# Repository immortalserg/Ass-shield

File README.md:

# Ass-shield
## Плата расширения для OrangePi Zero, OrangePi Zero plus, OrangePi Zero plus2, NanoPi Neo, NanoPi Neo Air, NanoPi Neo 2, NanoPi Neo Core, NanoPi Neo Core2, RaspberryPi Zero, BananaPi zero
### Функции
- Массив из 4-х микрофонов через процессор ADAU1772
- RF315/433 МГц приемник/передатчик (м.cx. SYN480R и SYN115)
- NRF24L01+
- zigbee cc2530 + cc2591
- 12 светодиодов WS2812B
- звук i2s ES9023 (только NanoPi) c усилителем 2х3Вт PAM8403 (PAM8404)
- часы реального времени DS3231
- 4 ИК светодиода для управления техникой
- диаметр 80 мм
- поддержска протокола Z-wave (USB stick или UART)
## Описание
- ИК передатчики (4 ИК диода через транзистор) подключены к GPIO26 (PA10) /NanoPi - PA0/
- 433 МГц приемник - GPIO15 (PA03) 
- 433 МГц передатчик - GPIO18 (PA18) /NanoPi PG8/
- 315 МГц приемник - GPIO12 (PA07) /NanoPi PG11/
- 315 МГц передатчик - GPIO16 (PA19) /NanoPi PG9/
- SI4432 - SPI1 (MOSI-GPIO19, MISO-GPIO21, CLK-GPIO23, NIRQ-GPIO13, NSEL-GPIO11)
- nrf24l01+ - SPI1 (MOSI-GPIO19, MISO-GPIO21, CLK-GPIO23, CS-GPIO24) /NanoPi SPI0 (MOSI-PC0, MISO-PC1, CLK-PC2, CS-PC3)/
- zigbee (cc2530) с усилителем cc2591 - UART1
- WS2812 LED - GPIO7 (PA06) 
- Часы реального времени DS3231 - i2c0
- i2c PCF8574 (P0- управление режимом записи 24LC256, P1-P4 - входы ADAU1772, P5 - MUTE  P6&P7 - Gain Select) 

Программирование ADAU1772 через i2c запись на микросхему памяти 24LC256, программирование: цифровые входы микрофонов, выходы аналоговые для OrangePi Zero, для остальных выход i2s в режиме ведомого.

J1 - питание 6-40V (1-VCC, 2-GND) на DC-DC преобразователь

J2 - DEBUG разъем для программирования cc2530 через (1-DC,2-DD,3-Reset,4-3.3V,5-GND)

J3 - питание 5В с DC-DC преобразователя (установить перемычку для питания через DC-DC преобразователь)

J4 - UART2 (1-3.3V, 2-RX, 3-TX, 4-GND) /нет для RaspberryPi Zero/

J5 - антенна NRF24L01+

J6 - i2s (1-WS, 2-CLK, 3-DIN) ADAU1772

J7 - выход на динамики (1-L+, 2-L-, 3-R+, 4-R-)

J8 - антенна zigbee (cc2530+cc2591)

### Переходная плата NanoPi Neo

J1 - переключение выхода звука 1,2-ON;3,4-OFF -- LINE / 1,2-OFF;3,4-ON -- i2s ES9023

### Переходная плата BananaPi zero, RaspberryPi Zero

J3 - переключатель i2s BananaPi Zero / RaspberryPi Zero

Для RaspberryPi Zero не используется LAN и UART2

## Изображения

## Переходная плата для NanoPi Neo

### Переходная плата BananaPi zero, RaspberryPi Zero

## Корпус

,

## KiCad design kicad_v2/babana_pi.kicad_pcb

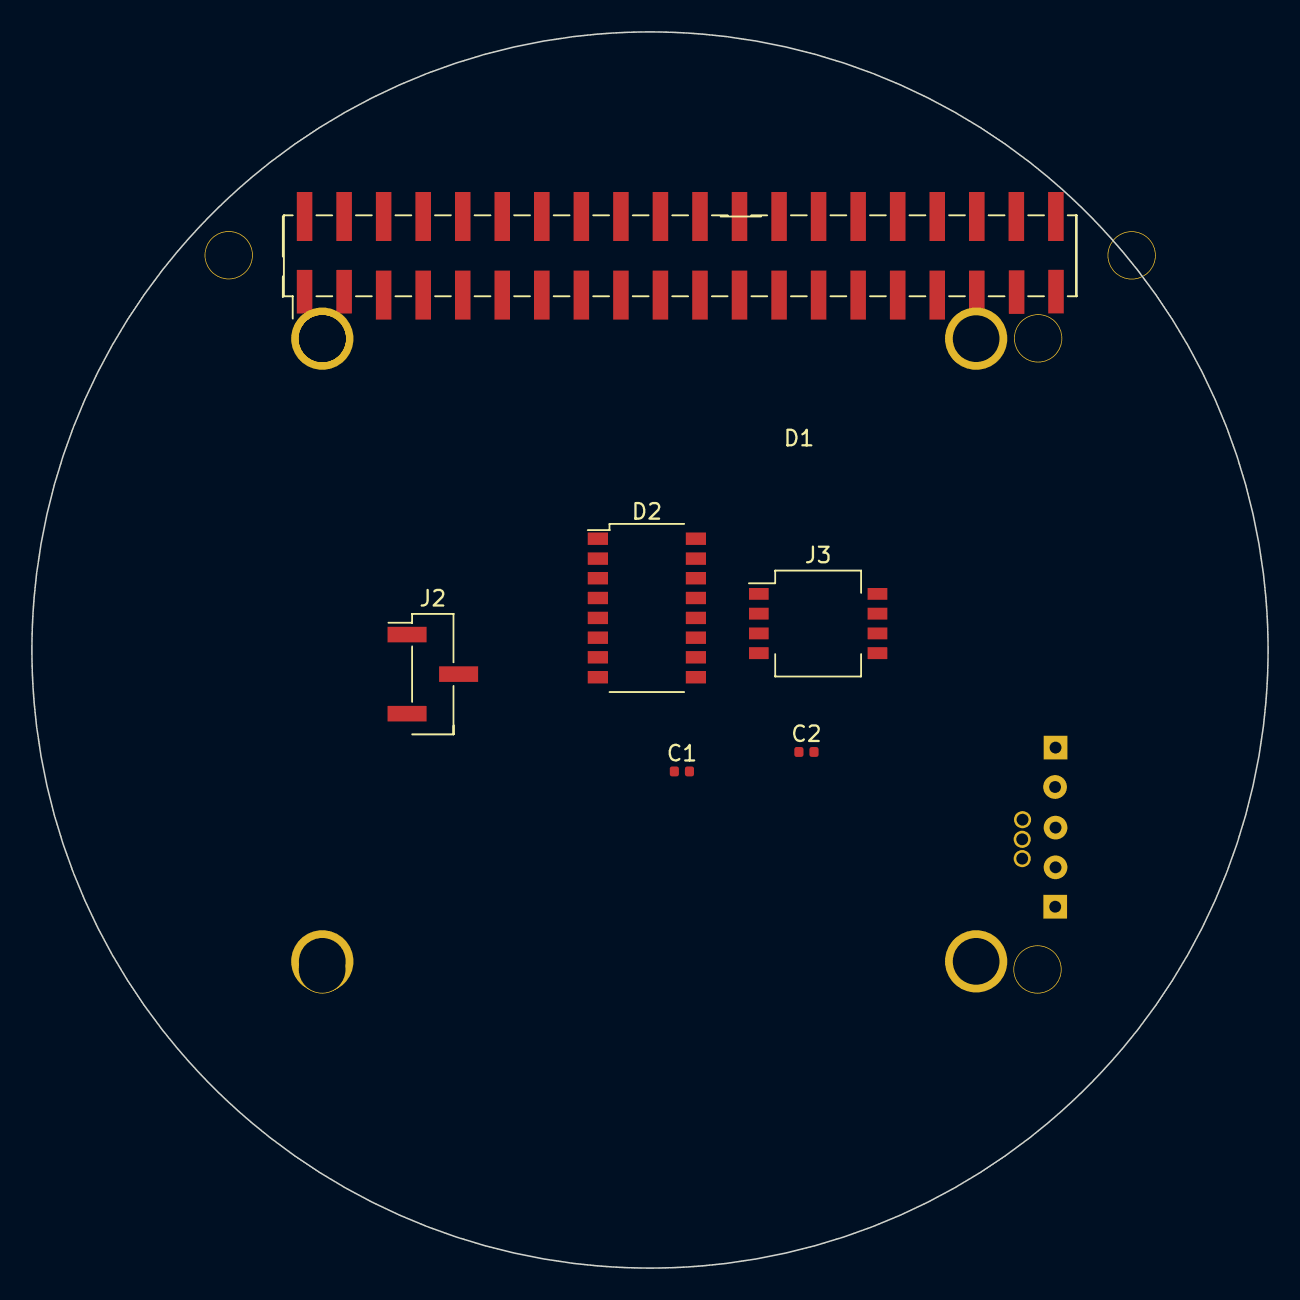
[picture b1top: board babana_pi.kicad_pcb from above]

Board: 2 copper layers, 79.4 x 79.4 mm, 7 parts (1 on the bottom side), 34 nets, no tracks yet.

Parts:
C1, C2: 1 µF; C_0402_1005Metric
D1: BananaPi
D2: ES9023; SOP-16_4.4x10.4mm_P1.27mm
J2: i2s; PinHeader_1x03_P2.54mm_Vertical_SMD_Pin1Left
J3: BananaPi/RaspberryPi; SW_DIP_SPSTx04_Slide_KingTek_DSHP04TS_W7.62mm_P1.27mm
U1: OPiZero-imm_lib; OPiZeroSMD

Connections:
3,3V: D1.17, D2.5, D2.6, U1.101
5V: D1.4, U1.102, U1.104
GND: C2.2, D2.12, D2.14, U1.2, U1.106, U1.109, U1.114, U1.120, U1.125, U1.201
IR: D1.18, U1.13
LL: D2.7, U1.8
LR: D2.8, U1.7
unnamed: C1.1, D2.10
unnamed: C1.2, D2.9
unnamed: C2.1, D2.11
unnamed: D1.12, J3.8
unnamed: D1.27, J3.5
unnamed: D1.28, J3.6
unnamed: D1.35, J3.7
PA02: D1.22, U1.122
PA03: D1.15, U1.115
PA07: D1.29, U1.112
PA10: D1.26, U1.126
PA18: D1.31, U1.118
PA19: D1.33, U1.116
PWM1: D1.7, U1.107
SCK: D1.5, U1.105
SDA: D1.3, U1.103
SPI1_CLK: D1.23, U1.123
SPI1_CS: D1.24, U1.124
SPI1_MISO: D1.21, U1.121
SPI1_MOSI: D1.19, U1.119
UART1_RX: D1.10, U1.110
UART1_TX: D1.8, U1.108
UART2_RX: D1.11, U1.111
UART2_TX: D1.13, U1.113
i2s-DIN: D1.38, J2.3
i2s_CLK: D2.1, J2.2, J3.2, J3.4
i2s_SDI: D1.40, D2.3
i2s_WS: D2.2, J2.1, J3.1, J3.3

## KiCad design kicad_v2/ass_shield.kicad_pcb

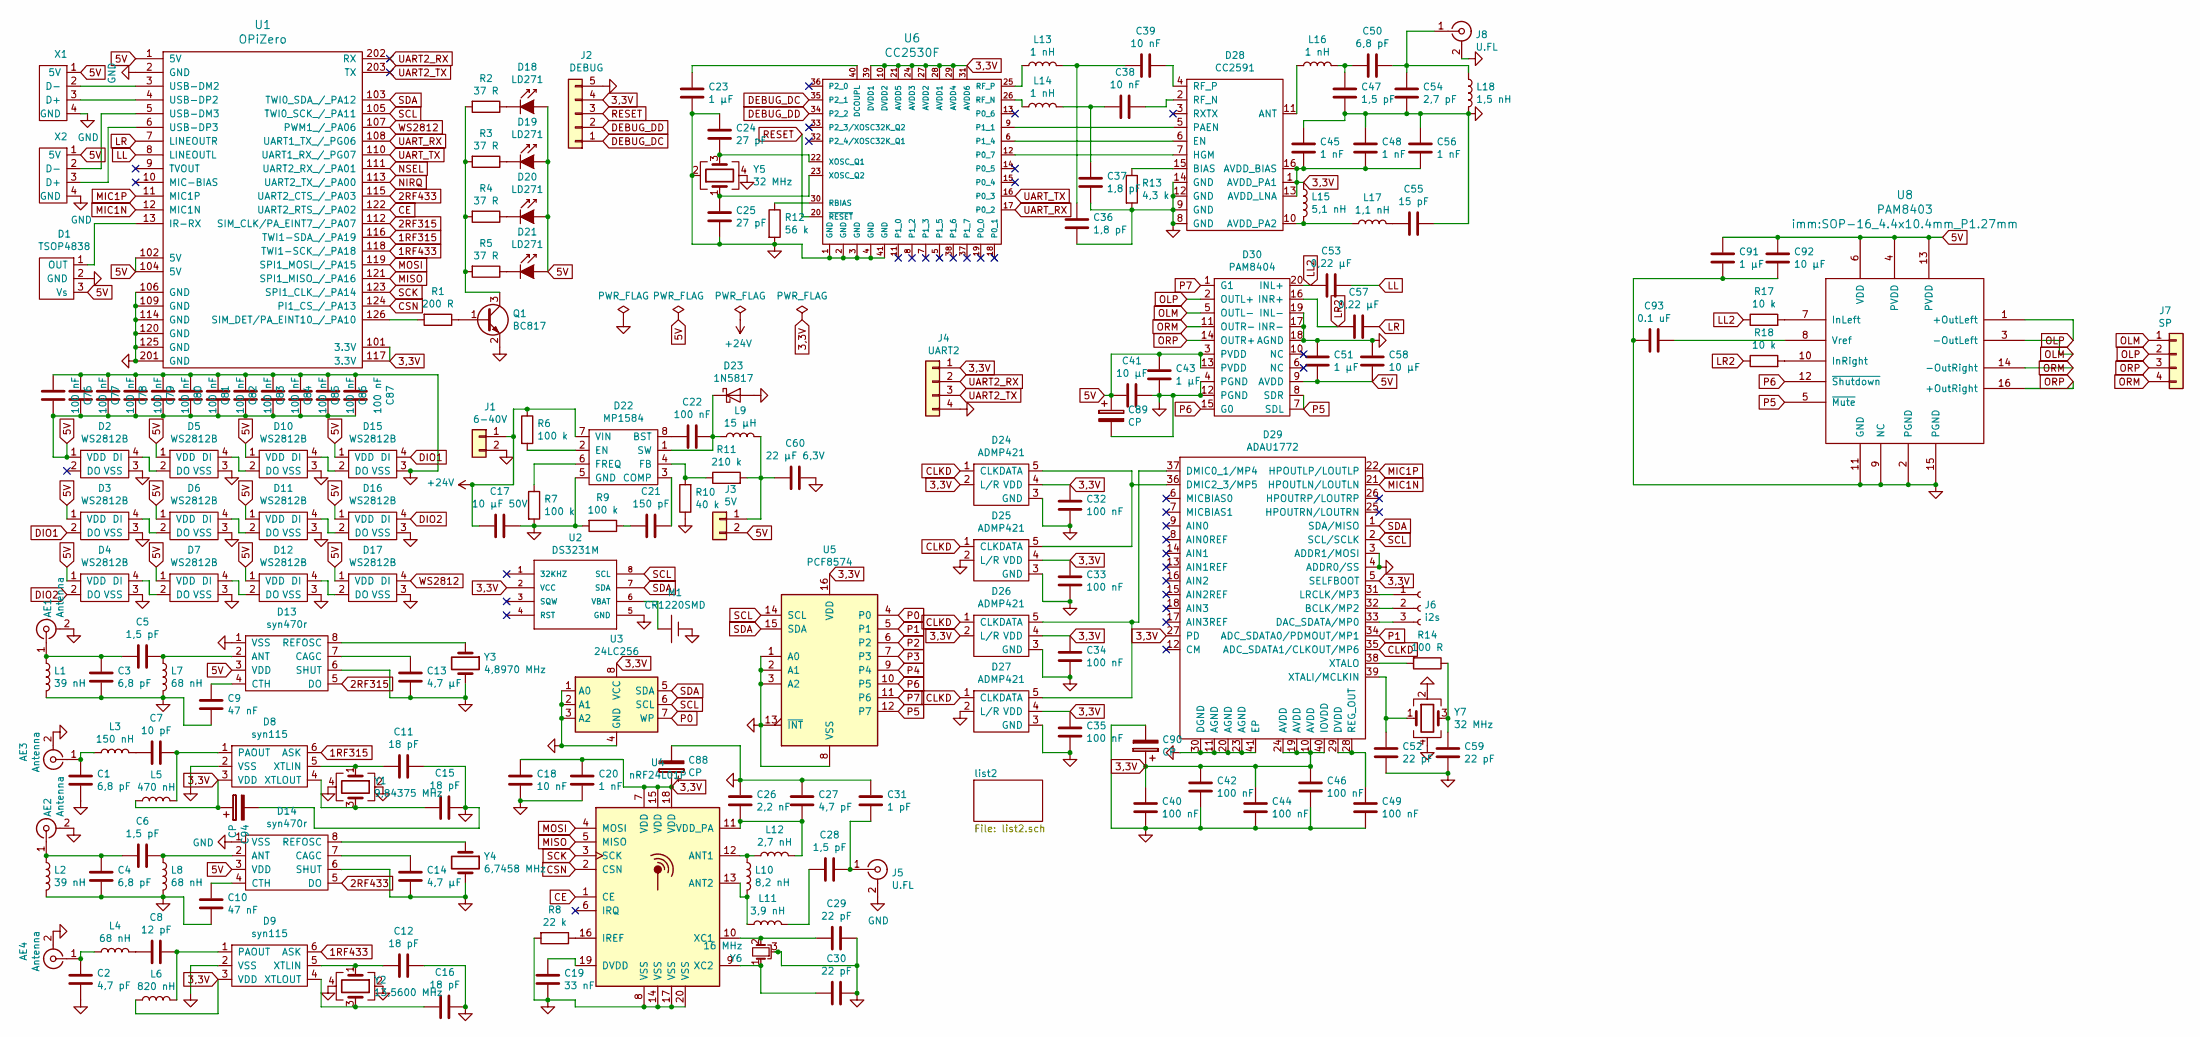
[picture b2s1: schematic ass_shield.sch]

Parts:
AE1, AE2, AE3, AE4: Antenna; U.FL_Hirose_U.FL-R-SMT-1_Vertical
C1, C3, C4, C50: 6,8 pF; C_0402_1005Metric
C2, C27: 4,7 pF; C_0402_1005Metric
C5, C6, C28, C47: 1,5 pF; C_0402_1005Metric
C7: 10 pF; C_0402_1005Metric
C8: 12 pF; C_0402_1005Metric
C9, C10: 47 nF; C_0402_1005Metric
C11, C12, C15, C16: 18 pF; C_0402_1005Metric
C13, C14: 4,7 µF; C_0402_1005Metric
C17: 10 µF 50V; C_1206_3216Metric
C18, C38, C39: 10 nF; C_0402_1005Metric
C19: 33 nF; C_0402_1005Metric
C20, C45, C48, C56: 1 nF; C_0402_1005Metric
C21: 150 pF; C_0402_1005Metric
C22, C32, C33, C34, C35, C40, C42, C44, C46, C49, C76, C77, C78, C79, C80, C81, C82, C83, C84, C85, C86, C87: 100 nF; C_0402_1005Metric
C23, C43, C51, C91: 1 µF; C_0402_1005Metric
C24, C25: 27 pF; C_0402_1005Metric
C26: 2,2 nF; C_0402_1005Metric
C29, C30, C52, C59: 22 pF; C_0402_1005Metric
C31: 1 pF; C_0402_1005Metric
C36, C37: 1,8 pF; C_0402_1005Metric
C41, C58, C92: 10 µF; C_0402_1005Metric
C53, C57: 0,22 µF; C_0402_1005Metric
C54: 2,7 pF; C_0402_1005Metric
C55: 15 pF; C_0402_1005Metric
C60: 22 µF 6,3V; C_1206_3216Metric
C88, C89, C90, C94: CP; C_1206_3216Metric
C93: 0.1 uF; C_0402_1005Metric
D1: TSOP4838; Vishay_MOLD-3Pin
D2, D3, D4, D5, D6, D7, D10, D11, D12, D15, D16, D17: WS2812B; ws2812b
D8, D9: syn115; SOT-23-6_Handsoldering
D13, D14: syn470r; SSOP-8_3.95x5.21x3.27mm_P1.27mm
D18, D19, D20, D21: LD271; LED_D3.0mm_Horizontal_O1.27mm_Z2.0mm_Clear
D22: MP1584; SOIC-8-1EP_3.9x4.9mm_P1.27mm_EP2.35x2.35mm
D23: 1N5817; D_SOD-323
D24, D25, D26, D27: ADMP421; ADMP421_2
D28: CC2591; QFN-16-1EP_4x4mm_P0.65mm_EP2.5x2.5mm
D29: ADAU1772; LFCSP-40-1EP
D30: PAM8404; QFN-20-1EP_4x4mm_P0.5mm_EP2.5x2.5mm
J1: 6-40V; PinHeader_1x02_P2.54mm_Vertical
J2: DEBUG; PinHeader_1x05_P1.27mm_Vertical
J3: 5V; PinHeader_1x02_P2.54mm_Vertical
J4: UART2; PinHeader_1x04_P2.54mm_Vertical_SMD_Pin1Left
J5, J8: U.FL; U.FL_Hirose_U.FL-R-SMT-1_Vertical
J6: i2s; PinSocket_1x03_P2.54mm_Vertical
J7: SP; PinHeader_1x04_P2.54mm_Vertical
L1, L2: 39 nH; L_0402_1005Metric
L3: 150 nH; L_0402_1005Metric
L4, L7, L8: 68 nH; L_0402_1005Metric
L5: 470 nH; L_0603_1608Metric
L6: 820 nH; L_0805_2012Metric
L9: 15 µH; CD54
L10: 8,2 nH; L_0402_1005Metric
L11: 3,9 nH; L_0402_1005Metric
L12: 2,7 nH; L_0402_1005Metric
L13, L14, L16: 1 nH; L_0402_1005Metric
L15: 5,1 nH; L_0402_1005Metric
L17: 1,1 nH; L_0402_1005Metric
L18: 1,5 nH; L_0402_1005Metric
M1: CR1220SMD; cr1220_smd
Q1: BC817; SOT-23
R1: 200 R; R_0402_1005Metric
R2, R3, R4, R5: 37 R; R_0402_1005Metric
R6, R7, R9: 100 k; R_0402_1005Metric
R8: 22 k; R_0402_1005Metric
R10: 40 k; R_0402_1005Metric
R11: 210 k; R_0402_1005Metric
R12: 56 k; R_0402_1005Metric
R13: 4,3 k; R_0402_1005Metric
R14: 100 R; R_0402_1005Metric
R17, R18: 10 k; R_0402_1005Metric
U1: OPiZero; OPiZero4
U2: DS3231M; SO-8_5.3x6.2mm_P1.27mm
U3: 24LC256; SOIC-8_3.9x4.9mm_P1.27mm
U4: nRF24L01P; QFN-20-1EP_4x4mm_P0.5mm_EP2.5x2.5mm
U5: PCF8574; QFN-16-1EP_3x3mm_P0.5mm_EP1.8x1.8mm
U6: CC2530F; QFN-40-1EP_6x6mm_P0.5mm_EP4.6x4.6mm
U8: PAM8403; SOP-16_4.4x10.4mm_P1.27mm
X1, X2: USB_F1; usb_f2
Y1: 9,84375 MHz; Crystal_SMD_5032-4Pin_5.0x3.2mm
Y2: 13,5600 MHz; Crystal_SMD_3225-4Pin_3.2x2.5mm
Y3: 4,8970 MHz; hc-49_smd
Y4: 6,7458 MHz; crystal_tc-26
Y5, Y7: 32 MHz; Crystal_SMD_3225-4Pin_3.2x2.5mm
Y6: 16 MHz; Crystal_SMD_3215-3Pin_3.2x1.5mm

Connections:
1RF315: D8.6 (ASK), U1.116 (TWI1-SDA_/_PA19)
1RF433: D9.6 (ASK), U1.118 (TWI1-SCK_/_PA18)
2RF315: D13.5 (DO), U1.112 (SIM_CLK/PA_EINT7_/_PA07)
2RF433: D14.5 (DO), U1.115 (UART2_CTS_/_PA03)
3,3V: C18.1, C20.1, C32.1, C33.1, C34.1, C35.1, C40.2, C42.2, C44.2, C45.1, C46.2, C48.1, C56.1, C88.1, C90.1, C94.1, D8.3 (VDD), D9.3 (VDD), D24.2 (L/R), D24.4 (VDD), D25.4 (VDD), D26.2 (L/R), D26.4 (VDD), D27.4 (VDD), D28.1 (AVDD_PA1), D28.13 (AVDD_LNA), D28.16 (AVDD_BIAS), D29.5 (SELFBOOT), D29.10 (AVDD), D29.19 (AVDD), D29.24 (AVDD), D29.27 (PD), D29.40 (IOVDD), J2.4, J4.1, L5.1, L6.1, L15.1, U1.101 (3.3V), U1.117 (3.3V), U2.2 (VCC), U3.8 (VCC), U4.7 (VDD), U4.15 (VDD), U4.18 (VDD), U5.16 (VDD), U6.10 (DVDD2), U6.21 (AVDD5), U6.24 (AVDD3), U6.27 (AVDD2), U6.28 (AVDD1), U6.29 (AVDD4), U6.31 (AVDD6), U6.39 (DVDD1)
5V: C41.2, C43.1, C51.1, C58.2, C76.1, C77.1, C78.1, C79.1, C80.1, C81.1, C82.1, C83.1, C84.1, C85.1, C86.1, C87.1, C89.1, C91.2, C92.1, D1.3 (Vs), D2.1 (VDD), D3.1 (VDD), D4.1 (VDD), D5.1 (VDD), D6.1 (VDD), D7.1 (VDD), D10.1 (VDD), D11.1 (VDD), D12.1 (VDD), D13.3 (VDD), D14.3 (VDD), D15.1 (VDD), D16.1 (VDD), D17.1 (VDD), D18.2 (A), D19.2 (A), D20.2 (A), D21.2 (A), D30.3 (PVDD), D30.9 (AVDD), D30.13 (PVDD), J3.2, U1.1 (5V), U1.102 (5V), U1.104 (5V), U8.4 (PVDD), U8.6 (VDD), U8.13 (PVDD), X1.1 (5V), X2.1 (5V)
+24V: C17.2, D22.7 (VIN), J1.1, R6.1
CE: U1.122 (UART2_RTS_/_PA02), U4.1 (CE)
CLKD: D24.1 (CLK), D25.1 (CLK), D26.1 (CLK), D27.1 (CLK), D29.35 (ADC_SDATA1/CLKOUT/MP6)
CSN: U1.124 (PI1_CS_/_PA13), U4.2 (CSN)
DEBUG_DC: J2.1, U6.35 (P2_1)
DEBUG_DD: J2.2, U6.34 (P2_2)
DIO1: D3.2 (DO), D15.4 (DI)
DIO2: D4.2 (DO), D16.4 (DI)
GND: AE1.2 (Ext), AE2.2 (Ext), AE3.2 (Ext), AE4.2 (Ext), C1.1, C2.1, C3.2, C4.2, C9.2, C10.2, C11.1, C12.1, C13.1, C14.1, C15.1, C16.1, C17.1, C18.2, C19.2, C20.2, C23.2, C24.1, C25.2, C26.1, C27.1, C29.1, C30.1, C31.1, C32.2, C33.2, C34.2, C35.2, C36.2, C37.2, C40.1, C41.1, C42.1, C43.2, C44.1, C45.2, C46.1, C47.1, C48.2, C49.1, C51.2, C52.1, C54.1, C55.1, C56.2, C58.1, C59.1, C60.1, C76.2, C77.2, C78.2, C79.2, C80.2, C81.2, C82.2, C83.2, C84.2, C85.2, C86.2, C87.2, C88.2, C89.2, C90.2, C91.1, C92.2, C93.2, C94.2, D1.2 (GND), D2.3 (VSS), D3.3 (VSS), D4.3 (VSS), D5.3 (VSS), D6.3 (VSS), D7.3 (VSS), D8.2 (VSS), D9.2 (VSS), D10.3 (VSS), D11.3 (VSS), D12.3 (VSS), D13.1 (VSS), D13.6 (SHUT), D14.1 (VSS), D14.6 (SHUT), D15.3 (VSS), D16.3 (VSS), D17.3 (VSS), D22.5 (GND), D22.9 (GND), D23.2 (A), D24.3 (GND), D25.2 (L/R), D25.3 (GND), D26.3 (GND), D27.2 (L/R), D27.3 (GND), D28.8 (GND), D28.9 (GND), D28.12 (GND), D28.14 (GND), D29.3 (ADDR1/MOSI), D29.4 (ADDR0/SS), D29.11 (AGND), D29.20 (AGND), D29.23 (AGND), D29.30 (DGND), D29.41 (EP), D30.4 (PGND), D30.12 (PGND), D30.17 (INR-), D30.18 (AGND), D30.19 (INL-), D30.21 (GND), J1.2, J2.5, J4.4, J5.2 (Ext), J8.2 (Ext), L1.2, L2.2, L7.2, L8.2, L18.2, M1.1 (-), Q1.2 (E), R7.2, R8.2, R9.2, R10.1, R12.2, R13.2, U1.2 (GND), U1.106 (GND), U1.109 (GND), U1.114 (GND), U1.120 (GND), U1.125 (GND), U1.201 (GND), U2.5 (GND), U3.1 (A0), U3.2 (A1), U3.3 (A2), U3.4 (GND), U4.8 (VSS), U4.14 (VSS), U4.17 (VSS), U4.20 (VSS), U5.1 (A0), U5.2 (A1), U5.3 (A2), U5.8 (VSS), U5.13 (~INT~), U5.17 (GND), U6.1 (GND), U6.2 (GND), U6.3 (GND), U6.4 (GND), U6.41 (GND), U8.2 (PGND), U8.9 (NC), U8.11 (GND), U8.15 (PGND), X1.4 (GND), X2.4 (GND), Y1.2, Y1.4, Y2.2, Y2.4, Y3.2, Y4.2, Y5.2, Y5.4, Y6.3, Y7.2, Y7.4; also elsewhere on the board
LL: C53.1, U1.8 (LINEOUTL)
LL2: C53.2, D30.20 (INL+), R17.1
LR: C57.1, U1.7 (LINEOUTR)
LR2: C57.2, D30.16 (INR+), R18.1
MIC1N: D29.21 (HPOUTLN/LOUTLN), U1.12 (MIC1N)
MIC1P: D29.22 (HPOUTLP/LOUTLP), U1.11 (MIC1P)
MISO: U1.121 (SPI1_MISO_/_PA16), U4.5 (MISO); also elsewhere on the board
MOSI: U1.119 (SPI1_MOSI_/_PA15), U4.4 (MOSI); also elsewhere on the board
NIRQ: U1.113 (UART2_TX_/_PA00); also elsewhere on the board
NSEL: U1.111 (UART2_RX_/_PA01); also elsewhere on the board
unnamed: AE1.1 (In), C3.1, C5.2, L1.1
unnamed: AE2.1 (In), C4.1, C6.2, L2.1
unnamed: AE3.1 (In), C1.2, L3.1
unnamed: AE4.1 (In), C2.2, L4.1
unnamed: C5.1, D13.2 (ANT), L7.1
unnamed: C6.1, D14.2 (ANT), L8.1
unnamed: C7.1, D8.1 (PAOUT), L5.2
unnamed: C7.2, L3.2
unnamed: C8.1, D9.1 (PAOUT), L6.2
unnamed: C8.2, L4.2
unnamed: C9.1, D13.4 (CTH)
unnamed: C10.1, D14.4 (CTH)
unnamed: C11.2, D8.5 (XTLIN), Y1.1
unnamed: C12.2, D9.5 (XTLIN), Y2.1
unnamed: C13.2, D13.7 (CAGC)
unnamed: C14.2, D14.7 (CAGC)
unnamed: C15.2, D8.4 (XTLOUT), Y1.3
unnamed: C16.2, D9.4 (XTLOUT), Y2.3
unnamed: C19.1, U4.19 (DVDD)
unnamed: C21.1, D22.3 (COMP)
unnamed: C21.2, R9.1
unnamed: C22.1, D22.1 (SW), D23.1 (K), L9.1
unnamed: C22.2, D22.8 (BST)
unnamed: C23.1, U6.40 (DCOUPL)
unnamed: C24.2, U6.22 (XOSC_Q1), Y5.3
unnamed: C25.1, U6.23 (XOSC_Q2), Y5.1
unnamed: C26.2, C27.2, L12.2, U4.11 (VDD_PA)
unnamed: C28.1, C31.2, J5.1 (In)
unnamed: C28.2, L11.2
unnamed: C29.2, U4.10 (XC1), Y6.2
unnamed: C30.2, U4.9 (XC2), Y6.1
unnamed: C36.1, C39.2, L13.2
unnamed: C37.1, C38.2, L14.2
unnamed: C38.1, D28.2 (RF_N)
unnamed: C39.1, D28.4 (RF_P)
unnamed: C47.2, C50.2, L16.2
unnamed: C49.2, D29.28 (REG_OUT), D29.29 (DVDD)
unnamed: C50.1, C54.2, J8.1 (In), L18.1
unnamed: C52.2, D29.39 (XTALI/MCLKIN), Y7.1
unnamed: C55.2, L17.2
unnamed: C59.2, R14.1, Y7.3
unnamed: C60.2, J3.1, L9.2, R11.2
unnamed: C93.1, U8.8 (Vref)
unnamed: D1.1 (OUT), U1.13 (IR-RX)
unnamed: D2.4 (DI), D5.2 (DO)
unnamed: D3.4 (DI), D6.2 (DO)
unnamed: D4.4 (DI), D7.2 (DO)
unnamed: D5.4 (DI), D10.2 (DO)
unnamed: D10.4 (DI), D15.2 (DO)
unnamed: D6.4 (DI), D11.2 (DO)
unnamed: D11.4 (DI), D16.2 (DO)
unnamed: D7.4 (DI), D12.2 (DO)
unnamed: D12.4 (DI), D17.2 (DO)
unnamed: D13.8 (REFOSC), Y3.1
unnamed: D14.8 (REFOSC), Y4.1
unnamed: D18.1 (K), R2.1
unnamed: D19.1 (K), R3.1
unnamed: D20.1 (K), R4.1
unnamed: D21.1 (K), R5.1
unnamed: D22.2 (EN), R6.2
unnamed: D22.4 (FB), R10.2, R11.1
unnamed: D22.6 (FREQ), R7.1
unnamed: D24.5 (DATA), D25.5 (DATA), D29.36 (DMIC2_3/MP5)
unnamed: D26.5 (DATA), D27.5 (DATA), D29.37 (DMIC0_1/MP4)
unnamed: D28.5 (PAEN), U6.9 (P1_1)
unnamed: D28.6 (EN), U6.6 (P1_4)
unnamed: D28.7 (HGM), U6.12 (P0_7)
unnamed: D28.10 (AVDD_PA2), L15.2, L17.1
unnamed: D28.11 (ANT), L16.1
unnamed: D28.15 (BIAS), R13.1
unnamed: D29.31 (LRCLK/MP3), J6.1
unnamed: D29.32 (BCLK/MP2), J6.2
unnamed: D29.33 (DAC_SDATA/MP0), J6.3
unnamed: D29.38 (XTALO), R14.2
unnamed: L10.1, L12.1, U4.12 (ANT1)
unnamed: L10.2, L11.1, U4.13 (ANT2)
unnamed: L13.1, U6.25 (RF_P)
unnamed: L14.1, U6.26 (RF_N)
unnamed: M1.2 (+), U2.6 (VBAT)
unnamed: Q1.1 (B), R1.1
unnamed: Q1.3 (C), R2.2, R3.2, R4.2, R5.2
unnamed: R1.2, U1.126 (SIM_DET/PA_EINT10_/_PA10)
unnamed: R8.1, U4.16 (IREF)
unnamed: R12.1, U6.30 (RBIAS)
unnamed: R17.2, U8.7 (InLeft)
unnamed: R18.2, U8.10 (InRight)
unnamed: U1.3 (USB-DM2), X1.2 (D-)
unnamed: U1.4 (USB-DP2), X1.3 (D+)
unnamed: U1.5 (USB-DM3), X2.2 (D-)
unnamed: U1.6 (USB-DP3), X2.3 (D+)
OLM: D30.5 (OUTL-), J7.1, U8.3 (-OutLeft)
OLP: D30.2 (OUTL+), J7.2, U8.1 (+OutLeft)
ORM: D30.11 (OUTR-), J7.4, U8.14 (-OutRight)
ORP: D30.14 (OUTR+), J7.3, U8.16 (+OutRight)
P0: U3.7 (WP), U5.4 (P0)
P1: D29.34 (ADC_SDATA0/PDMOUT/MP1), U5.5 (P1)
P5: D30.7 (SDL), D30.8 (SDR), U5.12 (P7), U8.5 (~Mute)
P6: D30.15 (G0), U5.10 (P5), U8.12 (~Shutdown)
P7: D30.1 (G1), U5.11 (P6)
RESET: J2.3, U6.20 (~RESET)
SCK: U1.123 (SPI1_CLK_/_PA14), U4.3 (SCK); also elsewhere on the board
SCL: D29.2 (SCL/SCLK), U1.105 (TWI0_SCK_/_PA11), U2.8 (SCL), U3.6 (SCL), U5.14 (SCL)
SDA: D29.1 (SDA/MISO), U1.103 (TWI0_SDA_/_PA12), U2.7 (SDA), U3.5 (SDA), U5.15 (SDA)
UART2_RX: J4.2, U1.202 (RX)
UART2_TX: J4.3, U1.203 (TX)
UART_RX: U1.108 (UART1_TX_/_PG06), U6.17 (P0_2)
UART_TX: U1.110 (UART1_RX_/_PG07), U6.16 (P0_3)
WS2812: D17.4 (DI), U1.107 (PWM1_/_PA06)

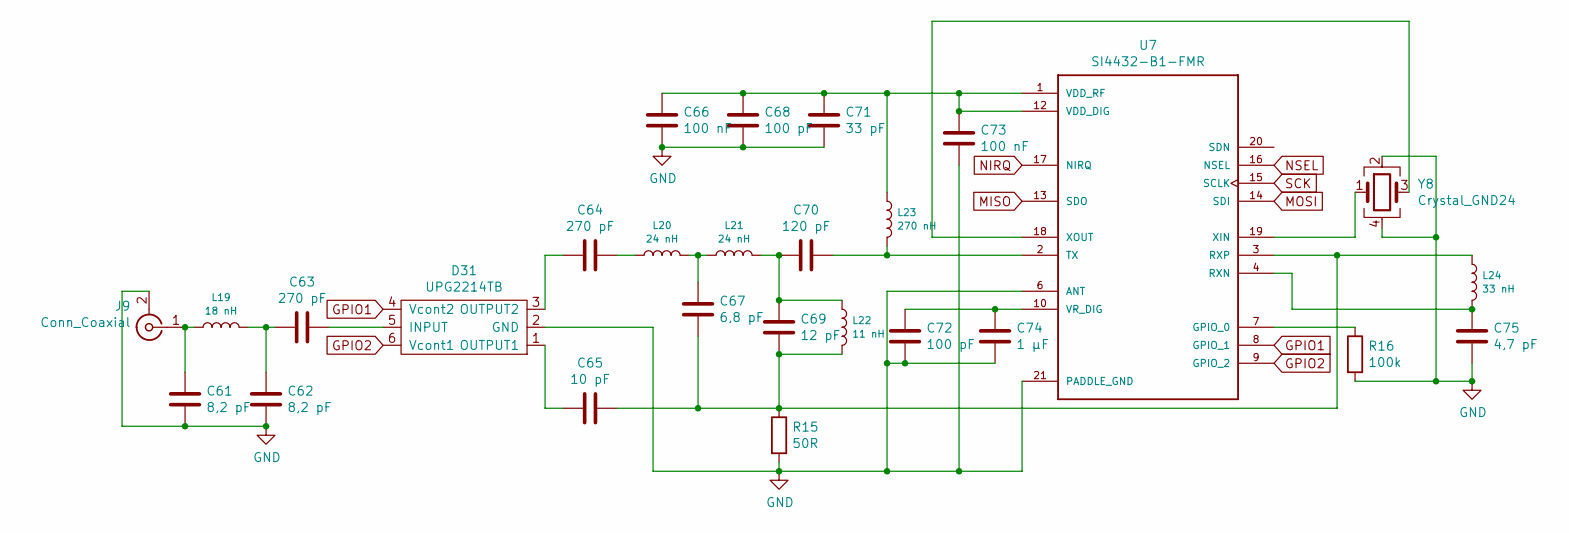
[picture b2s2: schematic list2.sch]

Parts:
C61, C62: 8,2 pF; C_0402_1005Metric
C63, C64: 270 pF; C_0402_1005Metric
C65: 10 pF; C_0402_1005Metric
C66, C73: 100 nF; C_0402_1005Metric
C67: 6,8 pF; C_0402_1005Metric
C68, C72: 100 pF; C_0402_1005Metric
C69: 12 pF; C_0402_1005Metric
C70: 120 pF; C_0402_1005Metric
C71: 33 pF; C_0402_1005Metric
C74: 1 µF; C_0402_1005Metric
C75: 4,7 pF; C_0402_1005Metric
D31: UPG2214TB; SOT-23-6
J9: Conn_Coaxial; U.FL_Hirose_U.FL-R-SMT-1_Vertical
L19: 18 nH; L_0402_1005Metric
L20, L21: 24 nH; L_0402_1005Metric
L22: 11 nH; L_0402_1005Metric
L23: 270 nH; L_0402_1005Metric
L24: 33 nH; L_0402_1005Metric
R15: 50R; R_0402_1005Metric
R16: 100k; R_0402_1005Metric
U7: SI4432-B1-FMR; QFN-20-1EP_4x4mm_P0.5mm_EP2.5x2.5mm
Y8: Crystal_GND24; Crystal_SMD_3225-4Pin_3.2x2.5mm

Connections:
GND: C61.1, C62.1, C66.1, C68.1, C71.1, C72.1, C73.1, C74.1, C75.1, D31.2 (GND), J9.2 (Ext), R15.2, R16.2, U7.6 (ANT), U7.21 (PADDLE_GND), Y8.2, Y8.4; also elsewhere on the board
GPIO1: D31.4 (Vcont2), U7.8 (GPIO_1)
GPIO2: D31.6 (Vcont1), U7.9 (GPIO_2)
MISO: U7.13 (SDO); also elsewhere on the board
MOSI: U7.14 (SDI); also elsewhere on the board
NIRQ: U7.17 (NIRQ); also elsewhere on the board
NSEL: U7.16 (NSEL); also elsewhere on the board
unnamed: C61.2, J9.1 (In), L19.1
unnamed: C62.2, C63.2, L19.2
unnamed: C63.1, D31.5 (INPUT)
unnamed: C64.1, L20.1
unnamed: C64.2, D31.3 (OUTPUT2)
unnamed: C65.1, C67.1, C69.1, L22.2, L24.1, R15.1, U7.3 (RXP)
unnamed: C65.2, D31.1 (OUTPUT1)
unnamed: C66.2, C68.2, C71.2, C73.2, L23.1, U7.1 (VDD_RF), U7.12 (VDD_DIG)
unnamed: C67.2, L20.2, L21.1
unnamed: C69.2, C70.2, L21.2, L22.1
unnamed: C70.1, L23.2, U7.2 (TX)
unnamed: C72.2, C74.2, U7.10 (VR_DIG)
unnamed: C75.2, L24.2, U7.4 (RXN)
unnamed: R16.1, U7.7 (GPIO_0)
unnamed: U7.18 (XOUT), Y8.3
unnamed: U7.19 (XIN), Y8.1
SCK: U7.15 (SCLK); also elsewhere on the board

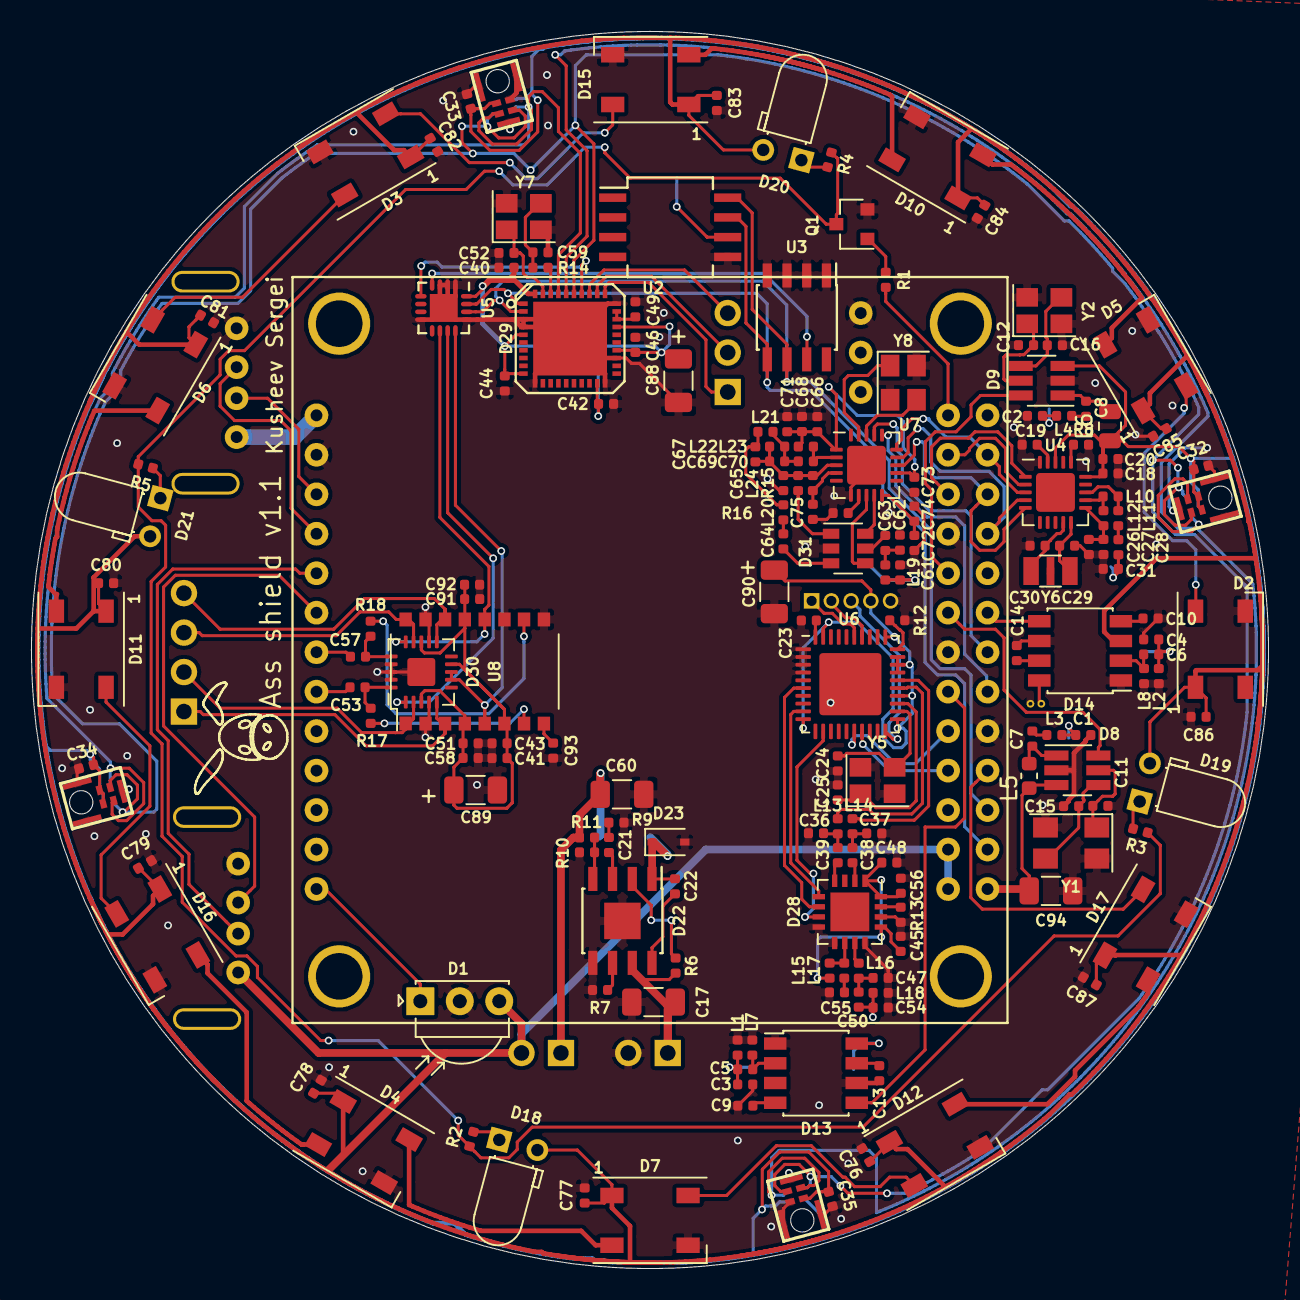
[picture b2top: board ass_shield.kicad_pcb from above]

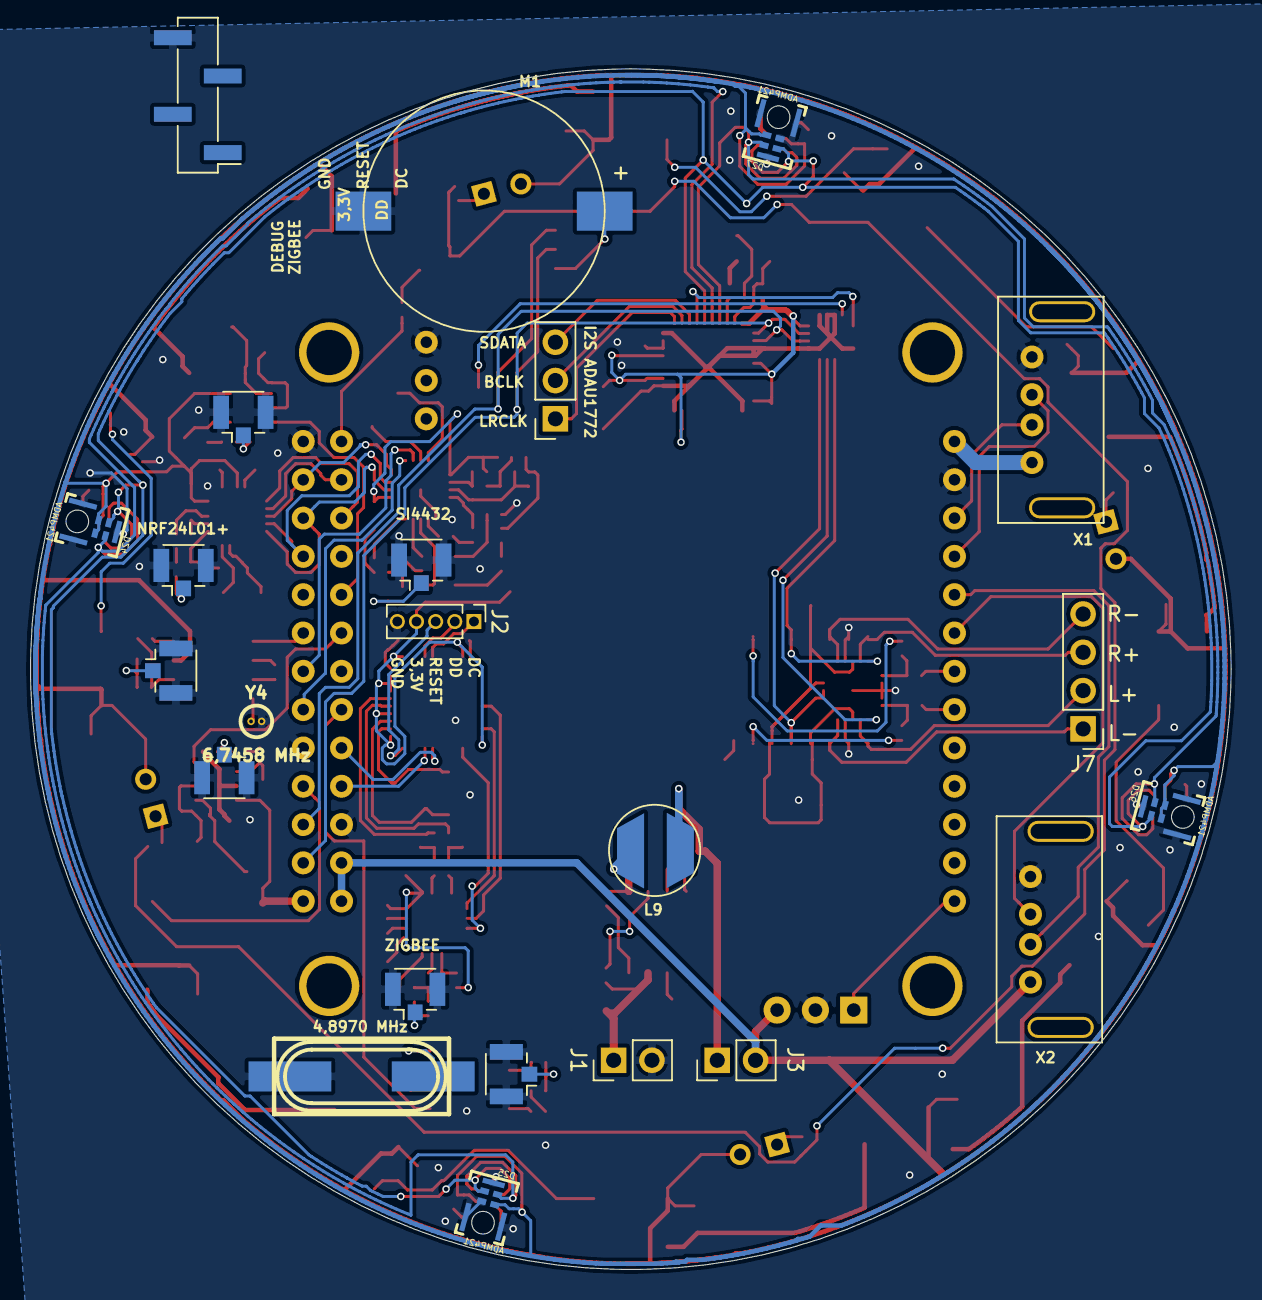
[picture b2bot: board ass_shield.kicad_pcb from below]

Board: 2 copper layers, 79.6 x 79.6 mm, 200 parts (19 on the bottom side), 151 nets.

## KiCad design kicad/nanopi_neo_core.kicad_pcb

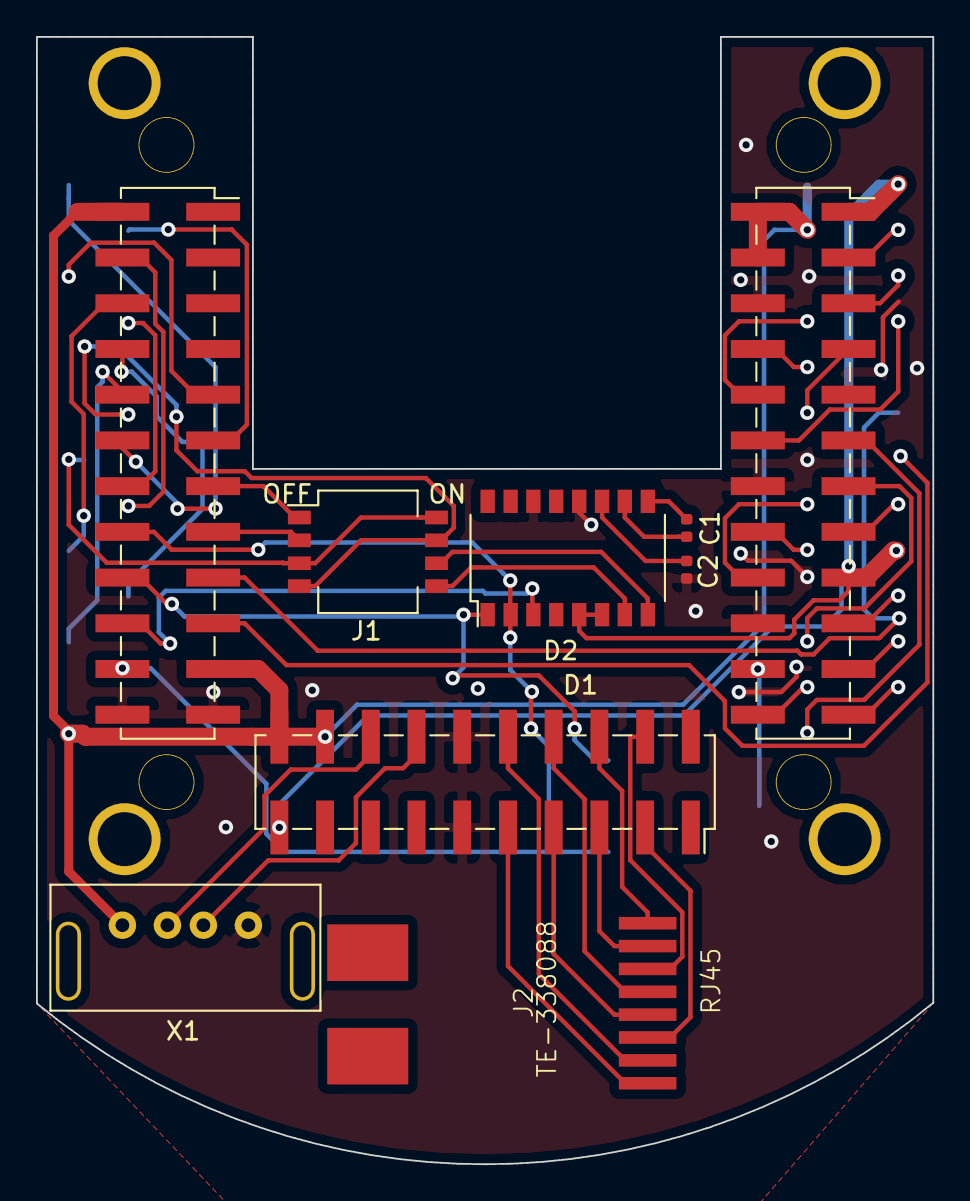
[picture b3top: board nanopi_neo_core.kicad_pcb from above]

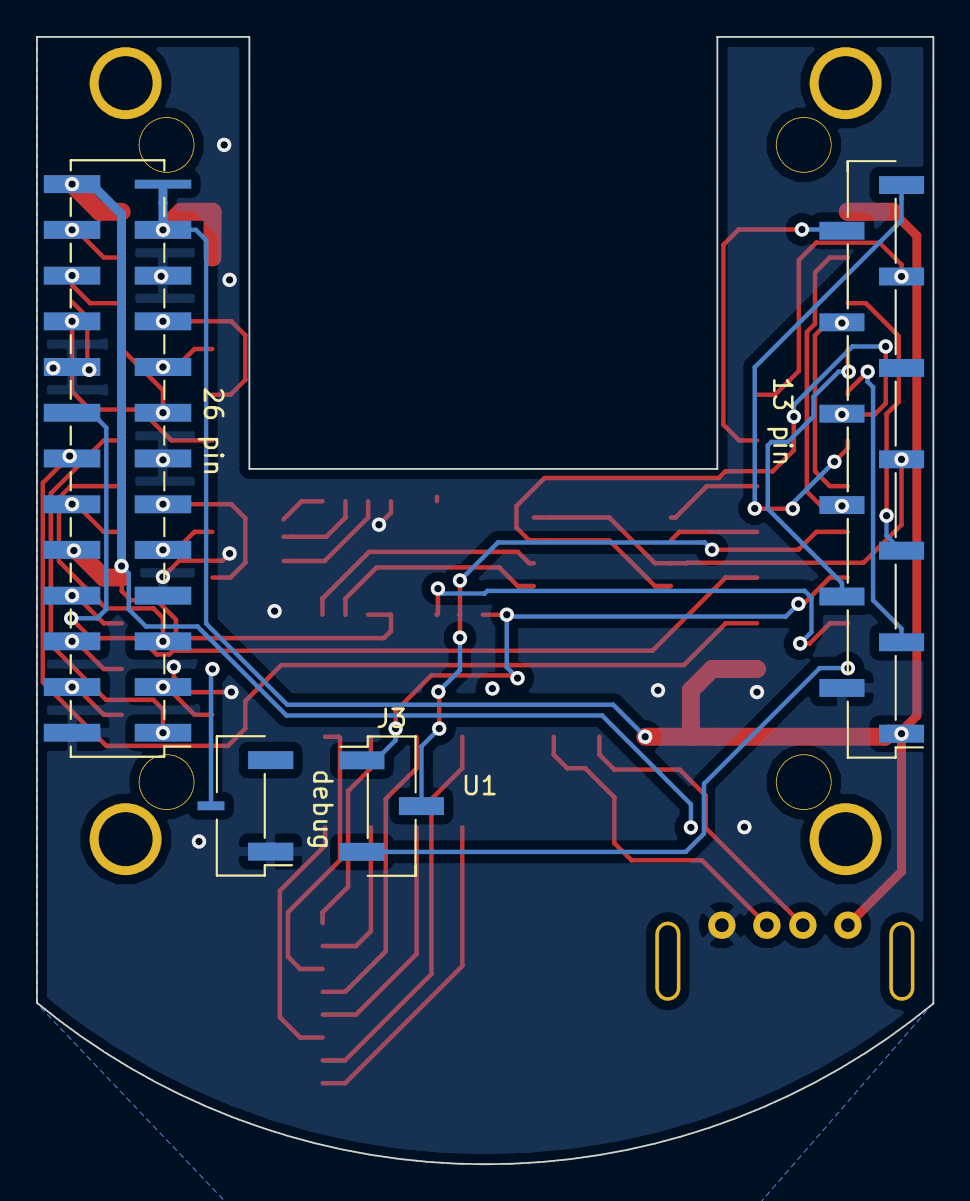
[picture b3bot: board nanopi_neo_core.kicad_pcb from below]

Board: 2 copper layers, 49.8 x 62.6 mm, 9 parts (2 on the bottom side), 52 nets.

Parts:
C1, C2: 1 µF; C_0402_1005Metric
D1: NanoPiNeo; NanoPiNeoAir2
D2: ES9023-imm_lib; SOP-16_4.4x10.4mm_P1.27mm
J1: HEADER-2x03; SW_DIP_SPSTx04_Slide_KingTek_DSHP04TS_W7.62mm_P1.27mm
J2: RJ45; RJ45-TE-338088
J3: Conn_01x03_Male; PinHeader_1x03_P2.54mm_Vertical_SMD_Pin1Left
U1: OPiZero-imm_lib; OPiZeroSMD
X1: USB_F1; usb_f2

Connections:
3,3V: D1.1, D1.17, D1.501, D2.5, D2.6, U1.101, U1.117
5V: D1.2, D1.4, D1.101, D1.203, D1.502, D1.504, U1.1, U1.102, U1.104, X1.1
DM2: D1.105, U1.3
DM3: D1.103, U1.5
DP2: D1.104, U1.4
DP3: D1.102, U1.6
GND: C2.2, D1.6, D1.9, D1.14, D1.20, D1.112, D1.204, D1.509, D1.510, D2.12, D2.14, U1.2, U1.106, U1.109, U1.114, U1.120, U1.125, U1.201, X1.4
IR: D1.106, U1.13
LL: J1.4, J1.7, U1.8
LR: J1.3, J1.8, U1.7
MBIAS: D1.107, U1.10
MN: D1.302, U1.12
MP: D1.301, U1.11
unnamed: C1.1, D2.10
unnamed: C1.2, D2.9
unnamed: C2.1, D2.11
unnamed: D1.108, D2.2, J3.2
unnamed: D1.109, D2.1, J3.1
unnamed: D1.110, D2.3
unnamed: D1.111, J3.3
unnamed: D1.303, J1.1
unnamed: D1.304, J1.2
unnamed: D1.506, X1.2
unnamed: D1.508, X1.3
unnamed: D1.511, J2.8
unnamed: D1.512, J2.7
unnamed: D1.513, J2.5
unnamed: D1.514, J2.4
unnamed: D1.515, J2.2
unnamed: D1.516, J2.1
unnamed: D1.517, J2.6
unnamed: D1.518, J2.3
unnamed: D2.7, J1.5
unnamed: D2.8, J1.6
PA02: D1.13, U1.122
PA03: D1.15, U1.115
PA07: D1.7, U1.112
PA10: D1.11, U1.126
PA18: D1.16, U1.118
PA19: D1.18, U1.116
PWM1: D1.12, U1.107
RX: D1.22, U1.202
SCK: D1.5, U1.105
SDA: D1.3, U1.103
SPI1_CLK: D1.23, U1.123
SPI1_CS: D1.24, U1.124
SPI1_MISO: D1.21, U1.121
SPI1_MOSI: D1.19, U1.119
UART1_RX: D1.8, U1.110
UART1_TX: D1.10, U1.108
UART2_RX: D1.201, U1.111
UART2_TX: D1.202, U1.113

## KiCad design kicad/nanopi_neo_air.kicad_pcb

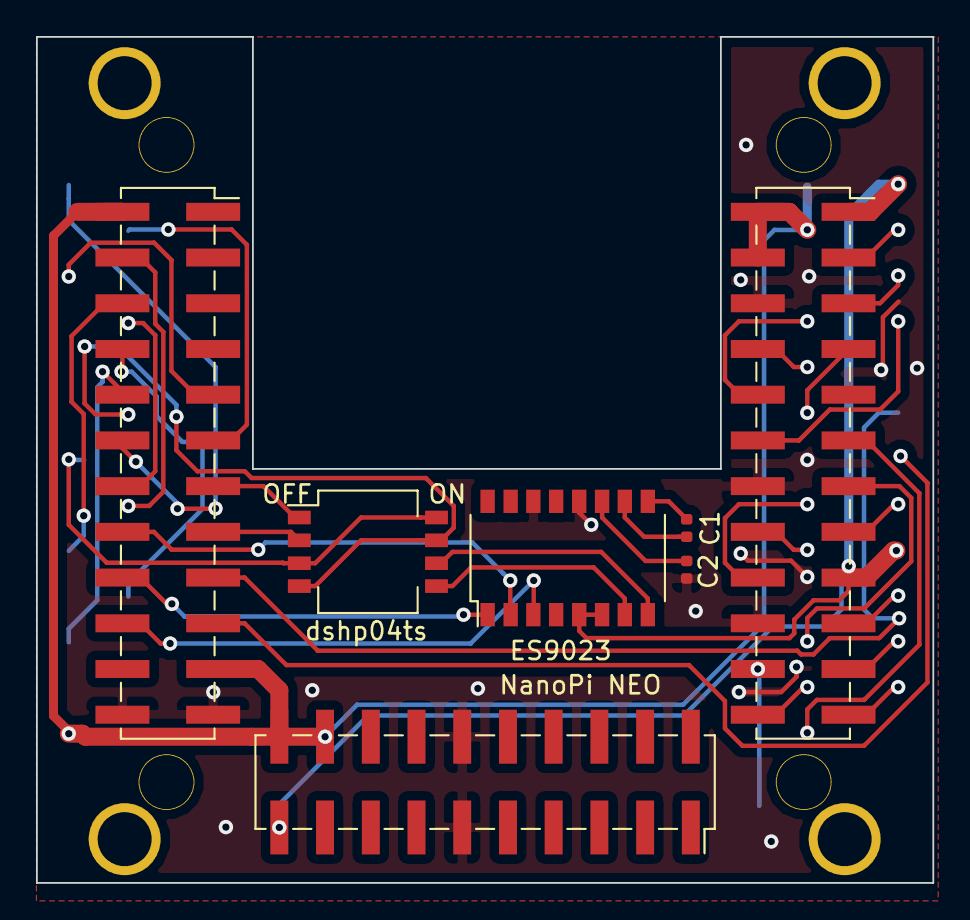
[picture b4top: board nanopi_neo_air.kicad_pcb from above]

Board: 2 copper layers, 49.8 x 47.0 mm, 6 parts (1 on the bottom side), 41 nets.

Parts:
Ass Shield: OPiZero-imm_lib; OPiZeroSMD
C1, C2: 1 µF; C_0402_1005Metric
ES9023: ES9023-imm_lib; SOP-16_4.4x10.4mm_P1.27mm
NanoPi NEO: NanoPiNeo; NanoPiNeoAir2
dshp04ts: HEADER-2x03; SW_DIP_SPSTx04_Slide_KingTek_DSHP04TS_W7.62mm_P1.27mm

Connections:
3,3V: Ass Shield.101, Ass Shield.117, ES9023.5, ES9023.6, NanoPi NEO.1, NanoPi NEO.17, NanoPi NEO.501
5V: Ass Shield.1, Ass Shield.102, Ass Shield.104, NanoPi NEO.2, NanoPi NEO.4, NanoPi NEO.101, NanoPi NEO.203, NanoPi NEO.502, NanoPi NEO.504
DM2: Ass Shield.3, NanoPi NEO.105
DM3: Ass Shield.5, NanoPi NEO.103
DP2: Ass Shield.4, NanoPi NEO.104
DP3: Ass Shield.6, NanoPi NEO.102
GND: Ass Shield.2, Ass Shield.106, Ass Shield.109, Ass Shield.114, Ass Shield.120, Ass Shield.125, Ass Shield.201, C2.2, ES9023.12, ES9023.14, NanoPi NEO.6, NanoPi NEO.9, NanoPi NEO.14, NanoPi NEO.20, NanoPi NEO.112, NanoPi NEO.204, NanoPi NEO.509, NanoPi NEO.510
IR: Ass Shield.13, NanoPi NEO.106
LL: Ass Shield.8, dshp04ts.4, dshp04ts.7
LR: Ass Shield.7, dshp04ts.3, dshp04ts.8
MBIAS: Ass Shield.10, NanoPi NEO.107
MN: Ass Shield.12, NanoPi NEO.302
MP: Ass Shield.11, NanoPi NEO.301
unnamed: C1.1, ES9023.10
unnamed: C1.2, ES9023.9
unnamed: C2.1, ES9023.11
unnamed: ES9023.2, NanoPi NEO.108
unnamed: ES9023.1, NanoPi NEO.109
unnamed: ES9023.3, NanoPi NEO.110
unnamed: NanoPi NEO.303, dshp04ts.1
unnamed: NanoPi NEO.304, dshp04ts.2
unnamed: ES9023.7, dshp04ts.5
unnamed: ES9023.8, dshp04ts.6
PA02: Ass Shield.122, NanoPi NEO.13
PA03: Ass Shield.115, NanoPi NEO.15
PA07: Ass Shield.112, NanoPi NEO.7
PA10: Ass Shield.126, NanoPi NEO.11
PA18: Ass Shield.118, NanoPi NEO.16
PA19: Ass Shield.116, NanoPi NEO.18
PWM1: Ass Shield.107, NanoPi NEO.12
RX: Ass Shield.202, NanoPi NEO.22
SCK: Ass Shield.105, NanoPi NEO.5
SDA: Ass Shield.103, NanoPi NEO.3
SPI1_CLK: Ass Shield.123, NanoPi NEO.23
SPI1_CS: Ass Shield.124, NanoPi NEO.24
SPI1_MISO: Ass Shield.121, NanoPi NEO.21
SPI1_MOSI: Ass Shield.119, NanoPi NEO.19
UART1_RX: Ass Shield.110, NanoPi NEO.8
UART1_TX: Ass Shield.108, NanoPi NEO.10
UART2_RX: Ass Shield.111, NanoPi NEO.201
UART2_TX: Ass Shield.113, NanoPi NEO.202

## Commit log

2018-01-20 Create OrangePi Zero pins
2018-01-20 Update OrangePi Zero pins
2018-11-01 edit
2018-11-01 a msg
